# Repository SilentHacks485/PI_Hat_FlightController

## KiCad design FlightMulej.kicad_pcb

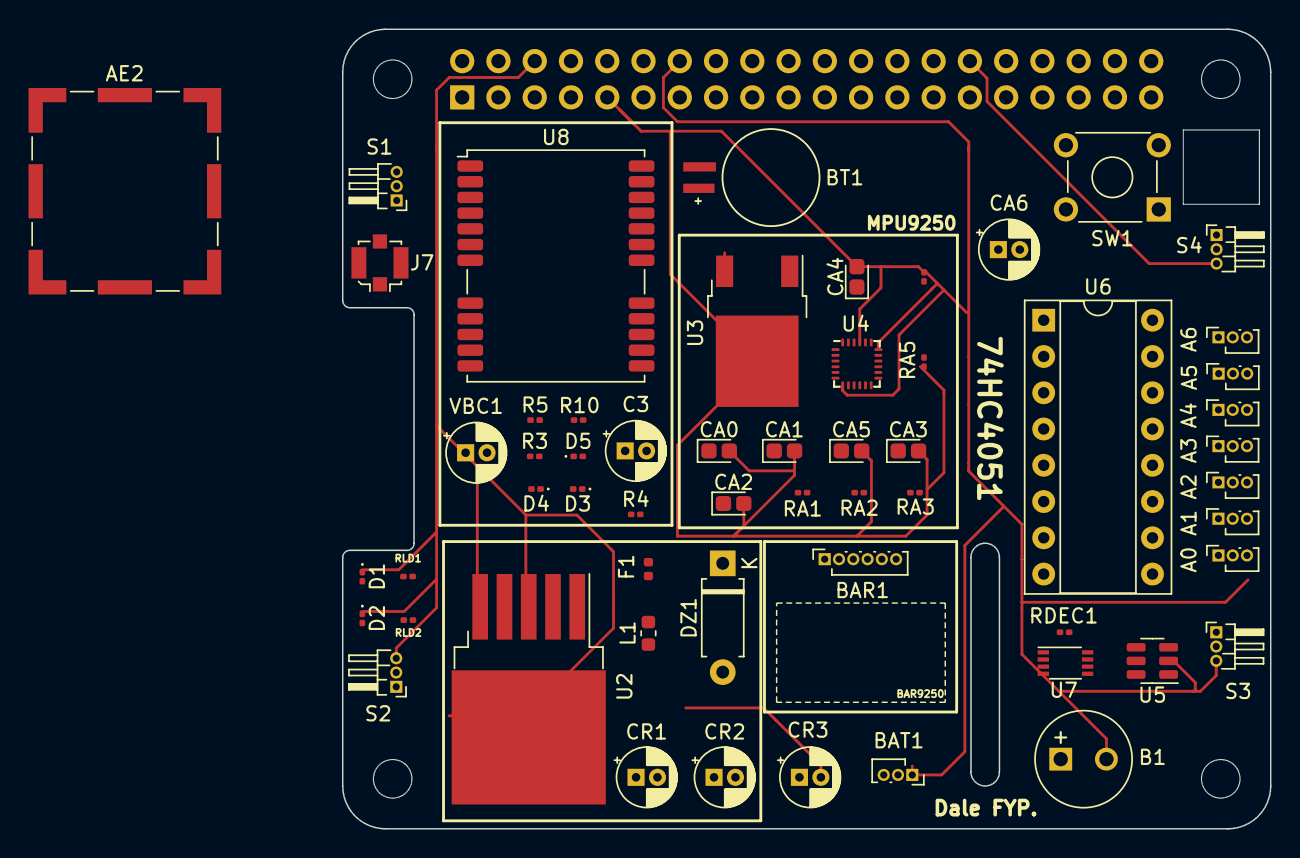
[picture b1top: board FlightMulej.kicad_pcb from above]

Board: 4 copper layers, 65.0 x 56.0 mm, 62 parts (1 on the bottom side), 30 nets.

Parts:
A0, A1, A2, A3, A4, A5, A6: Conn_01x03_Female; PinSocket_1x03_P1.00mm_Vertical
AE2: Antenna_Shield; Laird_Technologies_BMI-S-101_13.66x12.70mm
B1: Buzzer; MagneticBuzzer_Kingstate_KCG0601
BAR1: PinSocket_1x06_P1.00mm_Vertical
BAT1: Conn_01x03_Socket; PinSocket_1x03_P1.00mm_Vertical
BT1: MS621FE-FL11E; BAT_MS621FE-FL11E
C3: 1uF; CP_Radial_D4.0mm_P1.50mm
CA0: 4.7uF; CP_EIA-1608-08_AVX-J
CA1: 10uF; CP_EIA-1608-08_AVX-J
CA2, CA4, CA5: 100nF; CP_EIA-1608-08_AVX-J
CA3: 10nF; CP_EIA-1608-08_AVX-J
CA6: 4.7uF; CP_Radial_D4.0mm_P1.50mm
CR1, CR2: 100uF; CP_Radial_D4.0mm_P1.50mm
CR3: 1000uF; CP_Radial_D4.0mm_P1.50mm
D1, D2: LED; LED_0201_0603Metric
D3: ACT; LED_0201_0603Metric
D4: PWR; LED_0201_0603Metric
D5: D_Zener; D_0201_0603Metric
DZ1: D_Zener; D_A-405_P7.62mm_Horizontal
F1: 5A; Fuse_0402_1005Metric
J1: GPIO; PinSocket_2x20_P2.54mm_Vertical
J7: Conn_Coaxial; U.FL_Molex_MCRF_73412-0110_Vertical
L1: INDUCTOR; L_0603_1608Metric
MH1, MH2, MH3, MH4: MountingHole_2.7mm_M2.5
R3: 2.2k; R_0201_0603Metric
R4, R5: 220; R_0201_0603Metric
R10: 1k; R_0201_0603Metric
RA1, RA2, RA3, RA4, RA5: 10k; R_0201_0603Metric
RDEC1: 1k; R_0201_0603Metric
RLD1, RLD2: 1k; R_0201_0603Metric
S1, S2, S3, S4: Conn_01x03_Male; PinHeader_1x03_P1.00mm_Horizontal
SW1: SW_Push; SW_TH_Tactile_Omron_B3F-10xx
U2: LM2576HVS-5; TO-263-5_TabPin3
U3: LP38693DT-3.3; TO-252-2
U4: MPU-9250; InvenSense_QFN-24_3x3mm_P0.4mm
U5: ADS7866; TSOT-23-6
U6: 74HC4051; DIP-16_W7.62mm_Socket
U7: 74LVC2T45DC; VSSOP-8_2.3x2mm_P0.5mm
U8: NEO-M8N; ublox_NEO
VBC1: 100nF; CP_Radial_D4.0mm_P1.50mm

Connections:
+3.3V: R3.1, U4.1 (RESV_VDDIO), U5.1 (VDD), U8.1 (~SAFEBOOT), VBC1.1
+3V3: CA1.1, CA2.1, CA3.1, CA4.1, J1.1, J1.17, RA1.1, RA2.1, RA3.1, U3.1 (OUT), U4.8 (VDDIO), U4.13 (VDD), U6.6 (~E), U6.16 (VCC)
+5V: CA6.1, J1.2, RDEC1.1, RLD1.2, S1.1, S2.1, S3.1, S4.1
/GPIO[26]: B1.1 (-), J1.37
ADO: RA4.1, U4.9 (AD0/MISO)
CS: RA3.2, U4.22 (~CS)
FSYNC: RA5.1, U4.11 (FSYNC)
NEG_OUT: A0.3, A1.3, A2.3, A3.3, A4.3, A5.3, A6.3, B1.2 (+), BAT1.1, C3.2, CA0.2, CA1.2, CA2.2, CA3.2, CA4.2, CA5.2, CR1.1, CR2.2, CR3.2, D1.1 (K), D2.1 (K), D3.1 (K), D4.1 (K), D5.2 (A), DZ1.2 (A), F1.1, J1.6, J1.9, J1.14, J1.20, J1.25, J1.30, J1.34, J1.39, J7.2 (Ext), R3.2, R5.1, RA4.2, RA5.2, RLD2.2, S1.3, S2.3, S3.3, S4.3, U2.3 (GND), U2.5 (~ON/OFF), U3.2 (GND), U4.7 (AUX_SCL), U4.18 (GND), U4.21 (AUX_SDA), U5.2 (GND), U6.7 (VEE), U6.8 (GND), U8.4 (EXTINT), U8.5 (USB_DM), U8.6 (USB_DP), U8.7 (VDD_USB), U8.9 (VCC_RF), U8.10 (GND), U8.12 (GND), U8.13 (GND), U8.23 (VCC), U8.24 (GND), VBC1.2
unnamed: AE2.1 (A), J7.1 (In), U8.11 (RF_IN)
unnamed: A0.1, A1.1, A2.1, A3.1, A4.1, A5.1, A6.1
unnamed: BAT1.2, CR1.2, CR2.1, U2.1 (VIN)
unnamed: D1.2 (A), RLD1.1
unnamed: D2.2 (A), RLD2.1
unnamed: D3.2 (A), R4.2
unnamed: D4.2 (A), R5.2
unnamed: D5.1 (K), R10.1
unnamed: DZ1.1 (K), L1.1, U2.2 (OUT)
unnamed: CA5.1, U4.10 (REGOUT)
unnamed: U5.3 (AIN), U6.3 (A)
unnamed: U7.4 (GND), U7.5 (DIR)
unnamed: CA6.2, U7.8 (VCCB)
POS_OUT: CR3.1, F1.2, L1.2, U2.4 (FB)
S0: J1.36, U6.11 (S0)
S1: J1.38, U6.10 (S1)
S2: J1.40, U6.9 (S2)
SCL: RA1.2, U4.23 (SCL/SCLK)
SDA: RA2.2, U4.24 (SDA/MOSI)
TIMEPULSE: R4.1, U8.3 (TIMEPULSE)
VBACKUP: C3.1, R10.2, U8.22 (V_BCKP)
VCC: CA0.1, U3.3 (IN)

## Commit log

2023-08-28 Add files via upload
    This pcb was designed by Kicad
